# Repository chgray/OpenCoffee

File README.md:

# KiCad
 - to make the file load pcbnew and then do File->Fabrication Outputs.  save a .pos file {CSV, millimeters, seperate files for front/back} -> Generate Position File.  (chgray-keyboard-top-pos.csv)
	A) Change Ref to Designator
	B) Rot to Rotation
	C) Side to Layer
	D) PoxX to "Mid X"
	E) PosY to "Mid Y"
 
 - to make the BOM load eeschema and then do the button ("generate bill of material") BOM -> bom2csv
     you're looking for chgray-keyboard.csv
	A) Change Reference to "Designator"
	B) Change Datasheet to "JLCPCB Part #"
	C) Value to Comment

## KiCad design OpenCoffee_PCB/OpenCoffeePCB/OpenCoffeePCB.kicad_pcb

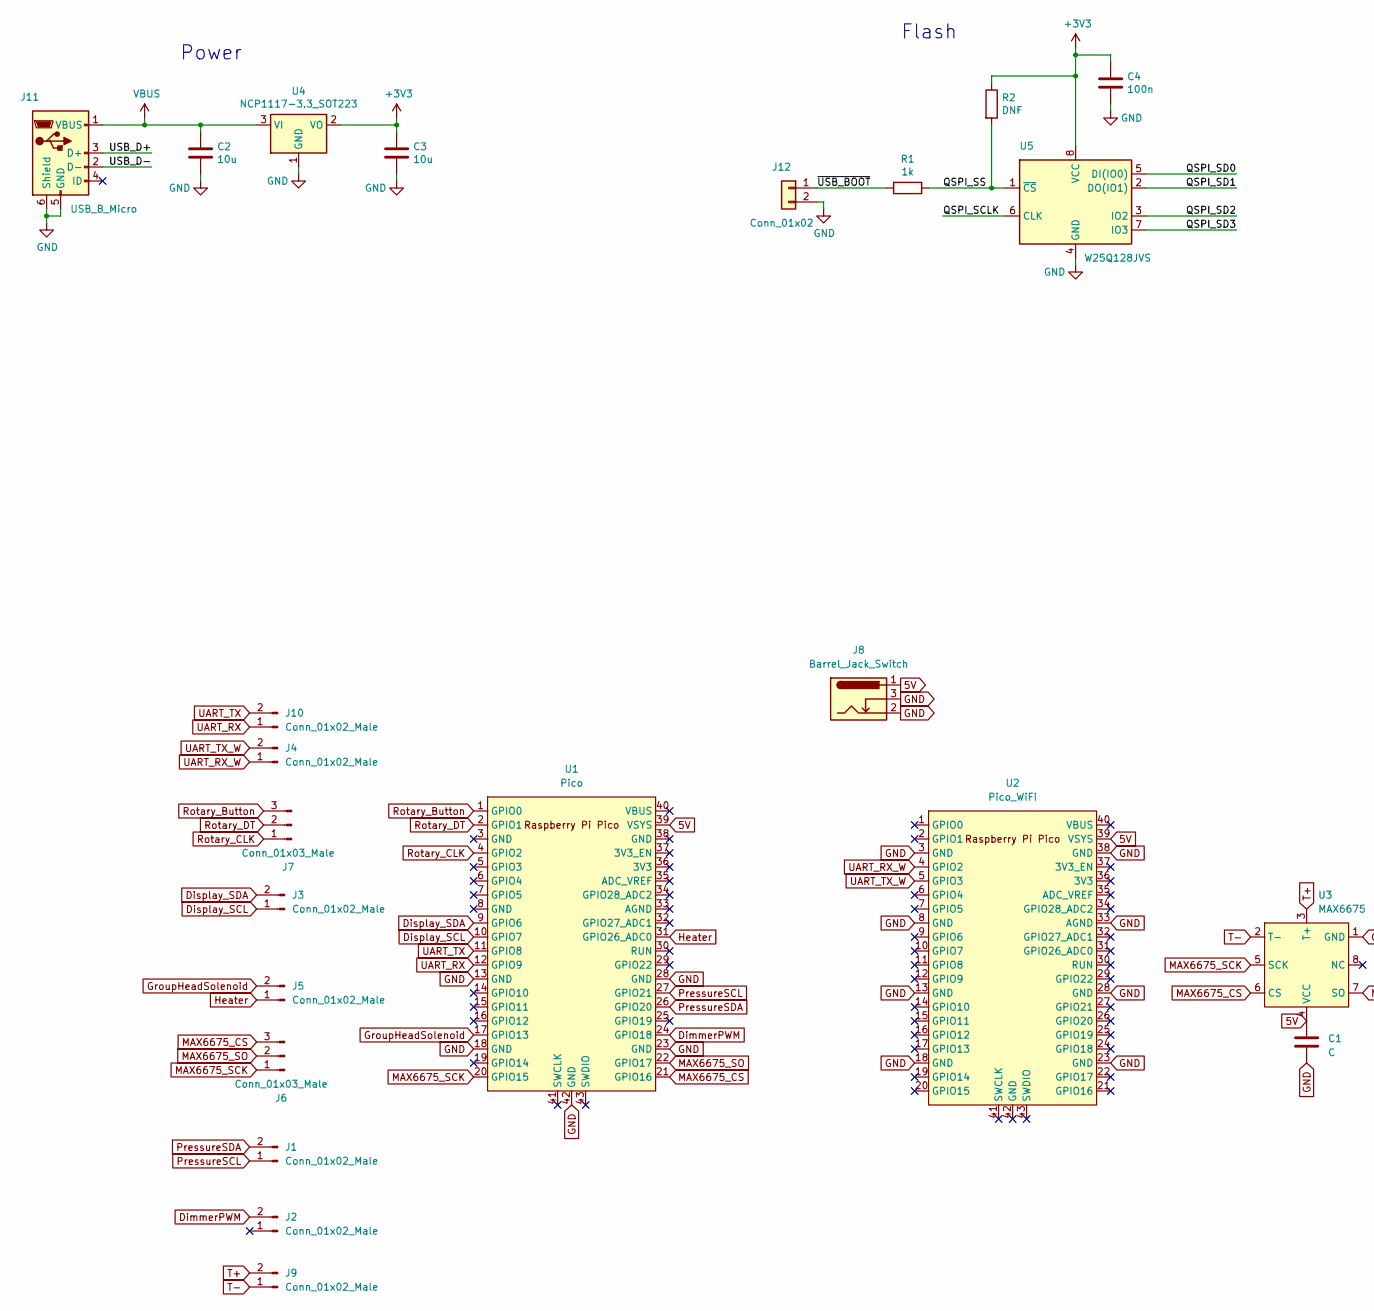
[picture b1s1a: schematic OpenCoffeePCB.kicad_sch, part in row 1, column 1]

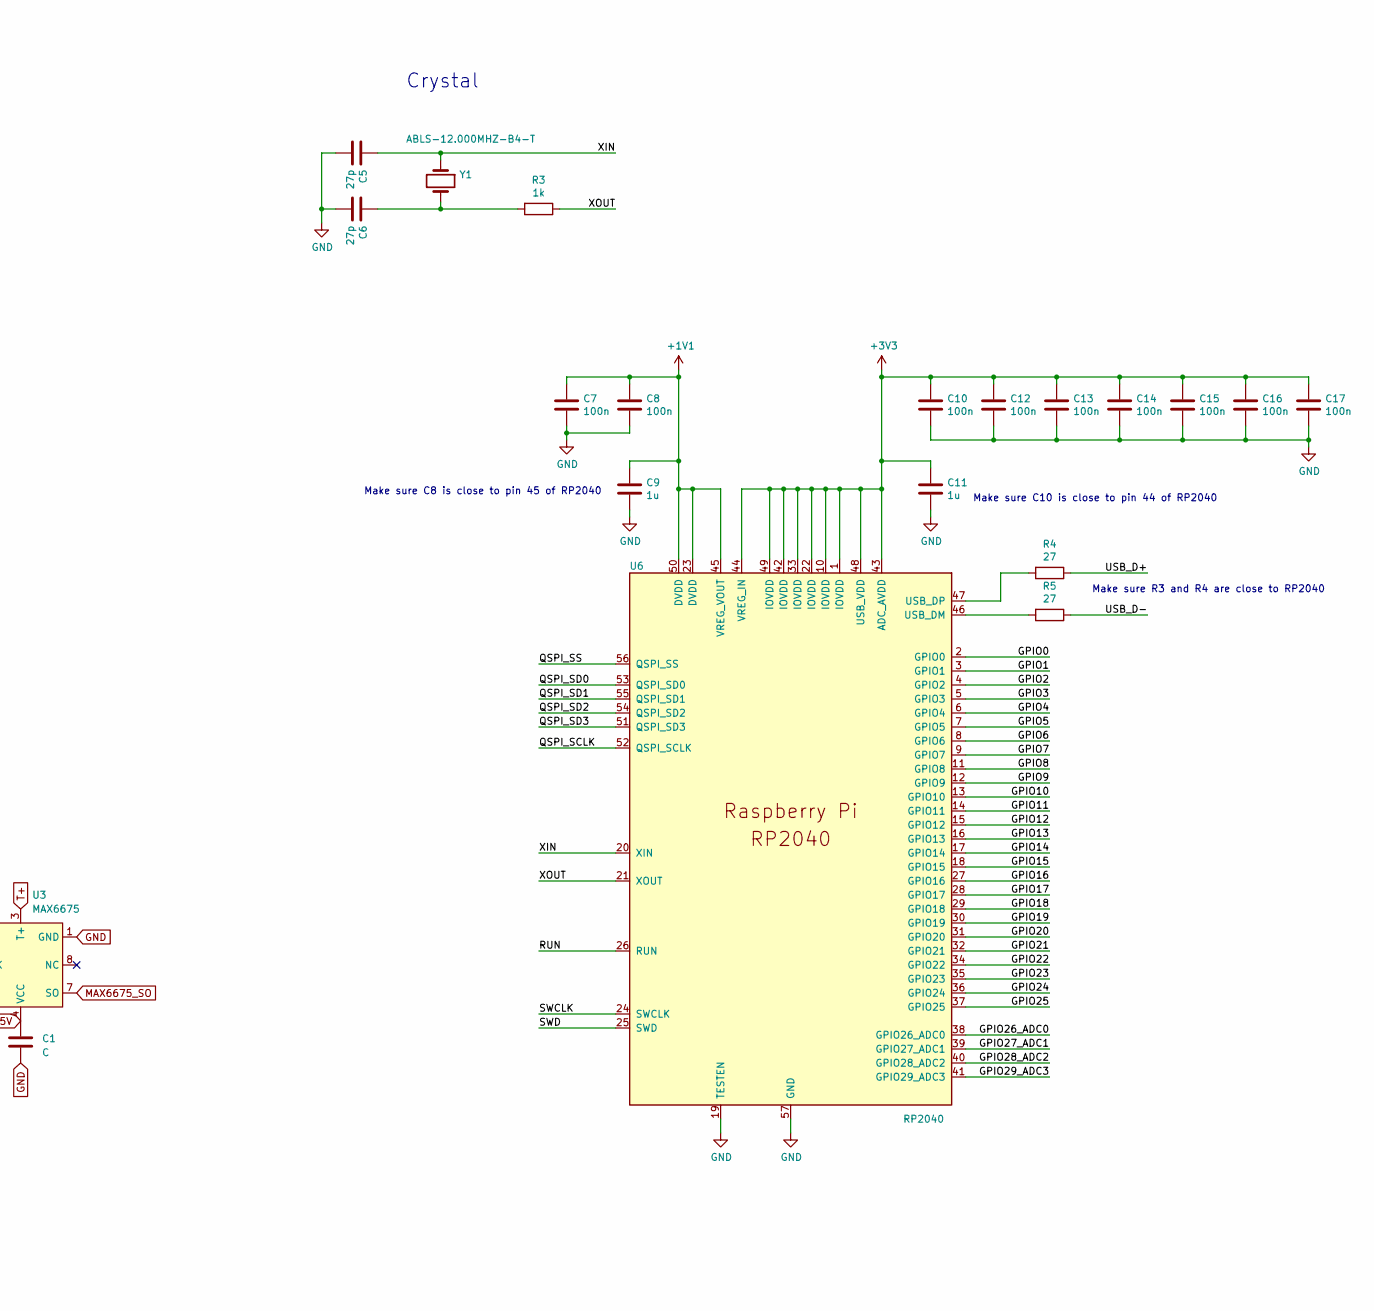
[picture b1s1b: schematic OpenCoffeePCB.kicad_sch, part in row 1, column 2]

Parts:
C1: C; C_0805_2012Metric
C2, C3: 10u; C_0805_2012Metric
C4, C7, C8, C10, C12, C13, C14, C15, C16, C17: 100n; C_0402_1005Metric
C5, C6: 27p; C_0402_1005Metric
C9, C11: 1u; C_0402_1005Metric
J1, J2, J3, J4, J5, J9, J10: Conn_01x02_Male; Molex_KK-254_AE-6410-02A_1x02_P2.54mm_Vertical
J6, J7: Conn_01x03_Male; Molex_KK-254_AE-6410-03A_1x03_P2.54mm_Vertical
J8: Barrel_Jack_Switch; BarrelJack_GCT_DCJ200-10-A_Horizontal
J11: USB_B_Micro; USB_Micro-B_Amphenol_10103594-0001LF_Horizontal_modified
J12: Conn_01x02; PinHeader_1x02_P2.54mm_Vertical
R1, R3: 1k; C_0402_1005Metric
R2: DNF; C_0402_1005Metric
R4, R5: 27; C_0402_1005Metric
U1: Pico; RPi_Pico_SMD_TH
U2: Pico_WiFi; RPi_Pico_SMD_TH_WIFI
U3: MAX6675
U4: NCP1117-3.3_SOT223; SOT-223-3_TabPin2
U5: W25Q128JVS; SOIC-8_5.23x5.23mm_P1.27mm
U6: RP2040; RP2040-QFN-56
Y1: ABLS-12.000MHZ-B4-T; Crystal_SMD_HC49-US

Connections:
5V: C1.1, J8.1, U1.39 (VSYS), U2.39 (VSYS), U3.4 (VCC)
+1V1: C7.1, C8.1, C9.1, U6.23 (DVDD), U6.45 (VREG_VOUT), U6.50 (DVDD)
+3V3: C3.1, C4.1, C10.1, C11.1, C12.1, C13.1, C14.1, C15.1, C16.1, C17.1, R2.1, U4.2 (VO), U5.8 (VCC), U6.1 (IOVDD), U6.10 (IOVDD), U6.22 (IOVDD), U6.33 (IOVDD), U6.42 (IOVDD), U6.43 (ADC_AVDD), U6.44 (VREG_IN), U6.48 (USB_VDD), U6.49 (IOVDD)
/GPIO0: U6.2 (GPIO0)
/GPIO1: U6.3 (GPIO1)
/GPIO2: U6.4 (GPIO2)
/GPIO3: U6.5 (GPIO3)
/GPIO4: U6.6 (GPIO4)
/GPIO5: U6.7 (GPIO5)
/GPIO6: U6.8 (GPIO6)
/GPIO7: U6.9 (GPIO7)
/GPIO8: U6.11 (GPIO8)
/GPIO9: U6.12 (GPIO9)
/GPIO10: U6.13 (GPIO10)
/GPIO11: U6.14 (GPIO11)
/GPIO12: U6.15 (GPIO12)
/GPIO13: U6.16 (GPIO13)
/GPIO14: U6.17 (GPIO14)
/GPIO15: U6.18 (GPIO15)
/GPIO16: U6.27 (GPIO16)
/GPIO17: U6.28 (GPIO17)
/GPIO18: U6.29 (GPIO18)
/GPIO19: U6.30 (GPIO19)
/GPIO20: U6.31 (GPIO20)
/GPIO21: U6.32 (GPIO21)
/GPIO22: U6.34 (GPIO22)
/GPIO23: U6.35 (GPIO23)
/GPIO24: U6.36 (GPIO24)
/GPIO25: U6.37 (GPIO25)
/GPIO26_ADC0: U6.38 (GPIO26_ADC0)
/GPIO27_ADC1: U6.39 (GPIO27_ADC1)
/GPIO28_ADC2: U6.40 (GPIO28_ADC2)
/GPIO29_ADC3: U6.41 (GPIO29_ADC3)
/QSPI_SCLK: U5.6 (CLK), U6.52 (QSPI_SCLK)
/QSPI_SD0: U5.5 (DI(IO0)), U6.53 (QSPI_SD0)
/QSPI_SD1: U5.2 (DO(IO1)), U6.55 (QSPI_SD1)
/QSPI_SD2: U5.3 (IO2), U6.54 (QSPI_SD2)
/QSPI_SD3: U5.7 (IO3), U6.51 (QSPI_SD3)
/QSPI_SS: R1.1, R2.2, U5.1 (~CS), U6.56 (QSPI_SS)
/RUN: U6.26 (RUN)
/SWCLK: U6.24 (SWCLK)
/SWD: U6.25 (SWD)
/USB_D+: J11.3 (D+), R4.1
/USB_D-: J11.2 (D-), R5.1
/XIN: C5.1, U6.20 (XIN), Y1.1
/XOUT: R3.1, U6.21 (XOUT)
/~USB_BOOT: J12.1, R1.2
DimmerPWM: J2.2, U1.24 (GPIO18)
Display_SCL: J3.1, U1.10 (GPIO7)
Display_SDA: J3.2, U1.9 (GPIO6)
GND: C1.2, C2.2, C3.2, C4.2, C5.2, C6.2, C7.2, C8.2, C9.2, C10.2, C11.2, C12.2, C13.2, C14.2, C15.2, C16.2, C17.2, J8.2, J8.3, J11.5 (GND), J11.6 (Shield), J12.2, U1.13 (GND), U1.18 (GND), U1.23 (GND), U1.28 (GND), U1.42 (GND), U2.3 (GND), U2.8 (GND), U2.13 (GND), U2.18 (GND), U2.23 (GND), U2.28 (GND), U2.33 (AGND), U2.38 (GND), U3.1 (GND), U4.1 (GND), U5.4 (GND), U6.19 (TESTEN), U6.57 (GND)
GroupHeadSolenoid: J5.2, U1.17 (GPIO13)
Heater: J5.1, U1.31 (GPIO26_ADC0)
MAX6675_CS: J6.3, U1.21 (GPIO16), U3.6 (CS)
MAX6675_SCK: J6.1, U1.20 (GPIO15), U3.5 (SCK)
MAX6675_SO: J6.2, U1.22 (GPIO17), U3.7 (SO)
unnamed: C6.1, R3.2, Y1.2
unnamed: R5.2, U6.46 (USB_DM)
unnamed: R4.2, U6.47 (USB_DP)
PressureSCL: J1.1, U1.27 (GPIO21)
PressureSDA: J1.2, U1.26 (GPIO20)
Rotary_Button: J7.3, U1.1 (GPIO0)
Rotary_CLK: J7.1, U1.4 (GPIO2)
Rotary_DT: J7.2, U1.2 (GPIO1)
T+: J9.2, U3.3 (T+)
T-: J9.1, U3.2 (T-)
UART_RX: J10.1, U1.12 (GPIO9)
UART_RX_W: J4.1, U2.4 (GPIO2)
UART_TX: J10.2, U1.11 (GPIO8)
UART_TX_W: J4.2, U2.5 (GPIO3)
VBUS: C2.1, J11.1 (VBUS), U4.3 (VI)

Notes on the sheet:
Make sure C8 is close to pin 45 of RP2040
Power
Make sure C10 is close to pin 44 of RP2040
Crystal
Flash
Make sure R3 and R4 are close to RP2040

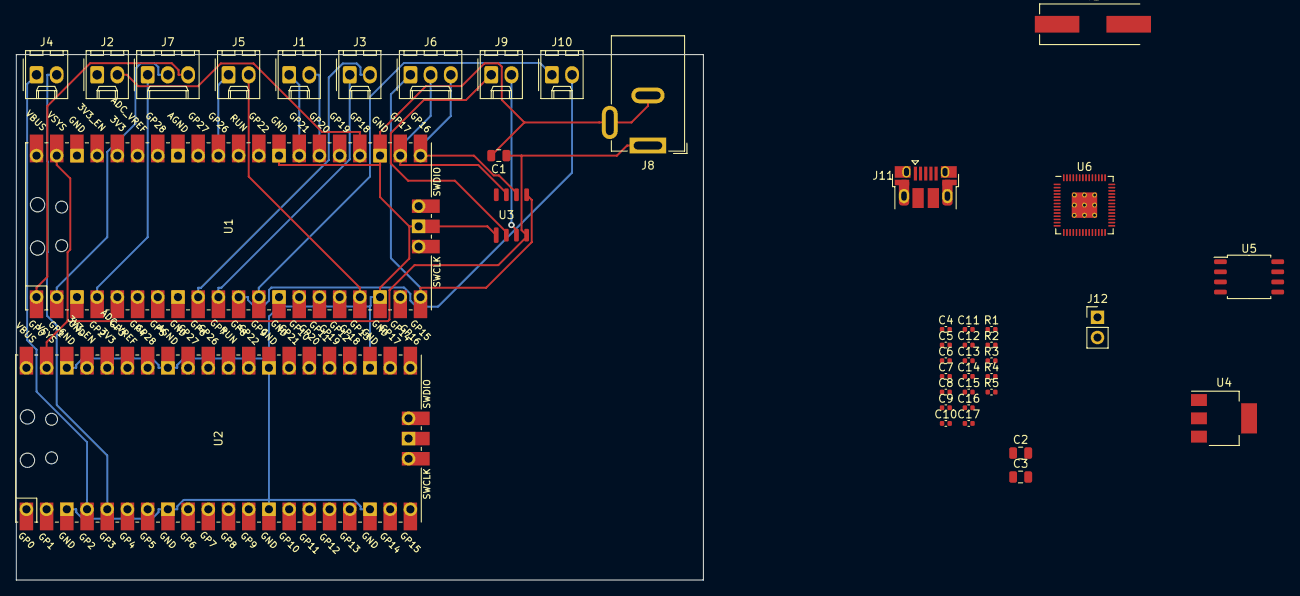
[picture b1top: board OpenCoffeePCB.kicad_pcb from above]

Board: 2 copper layers, 86.4 x 66.0 mm, 41 parts (0 on the bottom side), 38 nets.

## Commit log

2023-01-16 experimenting
2023-01-16 iterating
2023-01-16 test
2023-01-16 kinda
2023-01-16 change
2023-01-16 simple loop ok
2023-01-16 working
2023-01-16 chagnes
2023-01-17 stuff
2023-01-22 wifitest
2023-01-31 kinda going
2023-01-31 pid stuff
2023-02-03 heater
2023-02-07 cleaning up nice
2023-02-12 workin'
2023-02-13 plots
2023-02-13 steam finish
2023-02-20 fixing up wifi
2023-02-26 add pressure
2023-03-05 files
2023-03-06 add watchdog
2023-03-06 cleaning up
2023-03-06 new line
2023-03-06 relay commands over UART
2023-03-09 add refresh tool
2023-03-13 add dimmer to motor
2023-03-16 grind
2023-03-27 ADC experiment
2023-03-28 voltage working
2023-03-29 wifi work
2023-04-05 changing ux
2023-04-05 more simple
2023-04-06 add stuff
2023-04-06 udpates
2023-04-07 updates pcb
2023-04-10 merge
2023-04-10 update filename
2023-04-10 add hash alg
2023-04-10 update file
2023-04-10 working on auto update
2023-04-10 WifiRelay config
2023-04-12 working on chained update
2023-04-14 working on update
2023-04-14 almost
2023-04-14 updating hashs
2023-04-14 looking better
2023-04-15 working on serial
2023-04-23 Experiments
2023-04-23 almost working
2023-04-27 experiment
2023-05-23 add timer
2023-06-05 intial layout
2023-06-05 working on max6675
2023-06-11 working on pcb
2023-07-04 making PCB
2023-07-04 shipped pcb1
2023-07-05 add MAX6675
2023-07-05 part
2023-07-17 RP2040
2023-07-17 added RP2040 from https://datasheets.raspberrypi.com/rp2040/Minimal-KiCAD.zip?_gl=1*n2lfxt*_ga*MTI3MDcyNzk1MS4xNjg5NTU4NDUx*_ga_22FD70LWDS*MTY4OTU1ODQ1Mi4xLjEuMTY4OTU1OTgzMS4wLjAuMA..
2023-07-20 experiment with ssd1306
2023-08-24 blink
